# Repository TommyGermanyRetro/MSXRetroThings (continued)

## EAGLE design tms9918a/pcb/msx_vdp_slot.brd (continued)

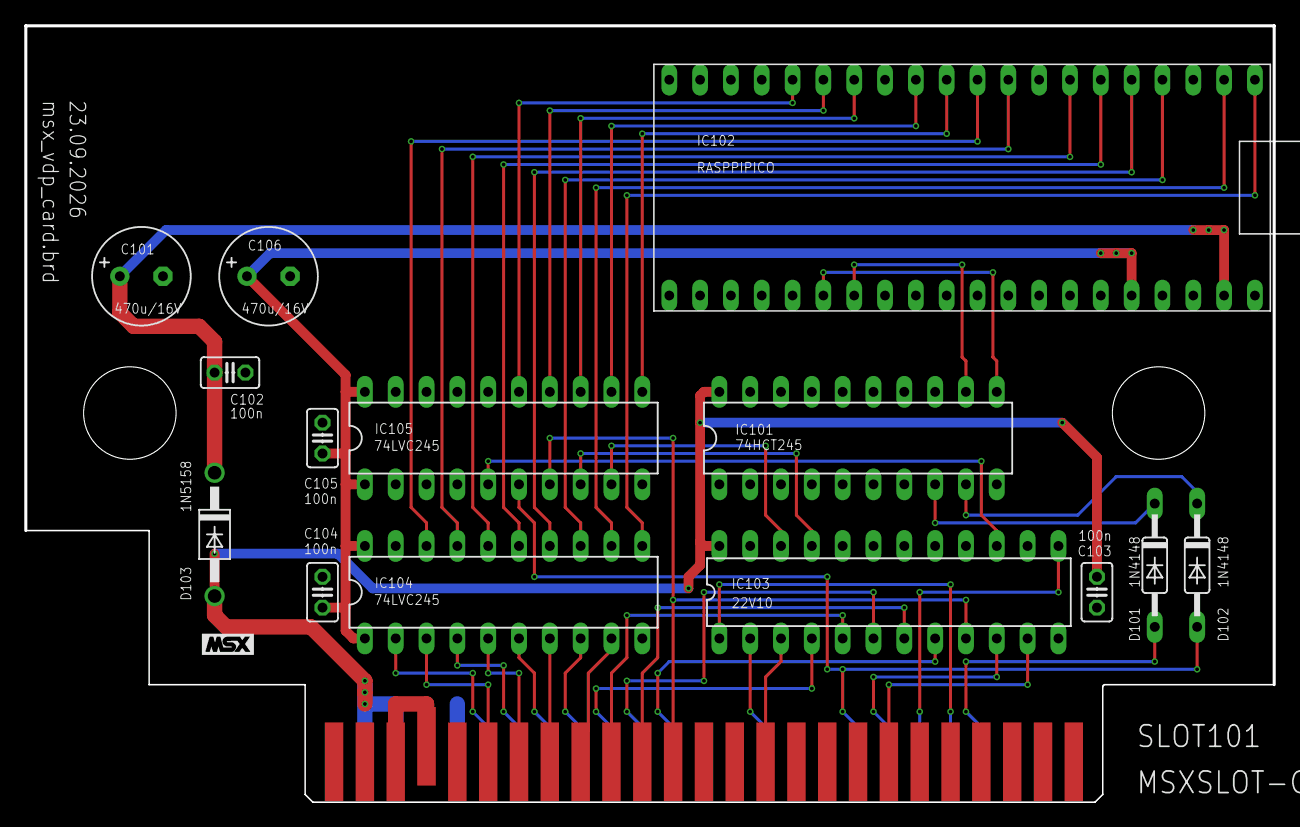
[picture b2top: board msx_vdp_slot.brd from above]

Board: 2 copper layers, 102.9 x 64.0 mm, 15 parts (0 on the bottom side), 47 nets.

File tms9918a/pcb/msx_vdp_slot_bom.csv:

Qty,Reference,Value,Package,Description
1,IC102,Raspberry Pi Pico,RASPPIPICO,"Raspberry Pi Pico (RP2040), flashed with TMS9918aPiPico.ino.uf2"
1,IC103,GAL22V10D,DIL24-3,"GAL22V10D-7LPN (or faster), programmed with gal/FPGA_IO.jed: decodes ports 98h/99h, /CSR and /CSW"
2,"IC104, IC105",74LVC245,DIL20,"Octal bus transceiver, slot to Pico (5 V tolerant in, 3.3 V out)"
1,IC101,74HCT245,DIL20,"Octal bus transceiver, Pico to slot (3.3 V in, 5 V out) for /WAIT and the reset of the MSX"
1,SLOT101,MSX card,MSXCARD,"MSX cartridge edge connector, 50 pins (2 x 25), 2.54 mm pitch, part of the board"
1,D103,1N5818,DO41-10,"Schottky diode, slot +5 V to Pico VSYS"
2,"D101, D102",1N4148,DO35-10,"Signal diode, 74HCT245 pulls /WAIT and /RESET of the slot only LOW"
2,"C101, C106",470u/16V,E3.5-8,"Electrolytic capacitor 470 uF 16 V, radial, 3.5 mm pitch, 8 mm diameter (C101 Pico VSYS, C106 +3.3 V)"
4,"C102, C103, C104, C105",100n,C025-025X050,"Ceramic capacitor 100 nF, 2.5 mm pitch"

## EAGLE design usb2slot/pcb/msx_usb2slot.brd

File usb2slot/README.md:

# USB2SLOT - real MSX cartridges in openMSX

USB2SLOT connects real MSX cartridges to the openMSX emulator on a Windows PC. A Teensy 4.1 on a small board
with two MSX cartridge slots generates the MSX clock and runs genuine Z80 bus cycles on the cartridges. openMSX
gets a new device, `USBSlot`, that forwards every memory and I/O access of its slot over USB to the board.

Tested with ROM cartridges (RCX, XIO), a cartridge with its own slot expander, the SD Mapper/Megaram 512K
cartridge (Nextor boots from its SD card, Memory Mapper and MegaRAM mode) and the RC2014 cards behind the RCX/XIO
cartridges (I/O, /INT and /WAIT), on emulated Spectravideo SVI-728 and Philips VG-8235 machines.

**Videos: booting Nextor from a real cartridge.** Both machines are emulated by openMSX, the cartridge is real: the SD Mapper/Megaram 512K sits in slot 2 of the board, and openMSX reaches it only over USB. From power-on, the machine scans its slots, finds the Nextor ROM of the cartridge, loads NEXTOR.SYS and COMMAND2.COM from the SD card of the cartridge and stops at the `A:\>` prompt. The videos were recorded in emulated time, so they run at the speed of a real MSX. With firmware protocol 3 the PC is faster than that: openMSX reaches the prompt of the VG-8235 after about 6 seconds, because the SD card sectors come over USB in one block each (see [CARTRIDGE_PROFILES.md](CARTRIDGE_PROFILES.md)). Click a picture to open the video.

Philips VG-8235 (MSX2), prompt after 18 seconds

Spectravideo SVI-728 (MSX1), prompt after 17 seconds

## Contents of this folder

| Folder | Content |
| --- | --- |
| [pcb](pcb) | Eagle project of the board: schematic `msx_usb2slot.sch`, layout `msx_usb2slot.brd`; bill of materials `msx_usb2slot_bom.csv`; photos |
| [case](case) | 3D-printable enclosure, bottom and top part as FreeCAD files `MSX_USB2SLOT_BOTTOM.FCStd` and `MSX_USB2SLOT_TOP.FCStd` |
| [pcb/gerber](pcb/gerber) | Gerber RS-274X and Excellon drill files of the two-layer board, also as `msx_usb2slot_gerber.zip` for the PCB maker |
| [firmware](firmware) | Teensy firmware `BridgeTeensy/BridgeTeensy.ino` and the ready-to-flash `BridgeTeensy.ino.hex` |
| [slotlink](slotlink) | PC library `slotlink.h` (Win32) and the test tool `slottest.exe` with its source |
| [openmsx](openmsx) | The `USBSlot` device (`USBSlot.cc/.hh`), start script, extensions, build scripts |
| [media](media) | Videos: start of a VG-8235 and an SVI-728 to the Nextor prompt |
| [CARTRIDGE_PROFILES.md](CARTRIDGE_PROFILES.md) | Recipe for cartridges with their own logic (slot expander, bank registers, SPI ports): detection, cache rules, block reads, measuring; worked example SD Mapper |
| [openmsx/bin](openmsx/bin) | Ready-to-run openMSX 21.0 for Windows x64 with the `USBSlot` device built in |

## 1. Hardware

- Teensy 4.1, two 50-pin MSX cartridge slots, level shifters 74HCT245 (Teensy to slot, 5 V) and 74LVC245 (slot to
  Teensy, 3.3 V); the data bus has one write path (74HCT245) and one read path (74LVC245).
- Power: external 5 V supply, at least 2 A (300 mA per slot plus Teensy and level shifters). +12 V and -12 V for the
  slots come from a DC-DC module. The Teensy is fed from the slot supply through a Schottky diode on VIN, so it
  stays powered whenever the slots are.
- If VIN and VUSB of the Teensy are connected (check with a continuity tester), the slot supply can feed current
  into the USB port of a switched-off PC. Keep that in mind when the PC is off and the cable stays plugged in.
- Jumper JP201: open for normal use. 1-2 connects the Teensy test line to /WAIT, 3-4 to /INT; both are only for
  the self test of the board (see section 3).
- No hot plug, just like a real MSX: change cartridges only with the board switched off.
- To order the board, upload `pcb/gerber/msx_usb2slot_gerber.zip` to the PCB maker. Check the layers in a Gerber
  viewer (for example the online viewer of the PCB maker) before you order. The parts are listed in
  `pcb/msx_usb2slot_bom.csv`.

### Enclosure

`case` holds a two-part enclosure for the board (outside 150 x 115 mm; bottom part 10 mm, top part
30 mm high) as FreeCAD files, built with FreeCAD 1.0 (PartDesign: sketches, pads, pockets). Only the
design files are included, no STL or G-code, so the enclosure can be adapted, for example to other
cartridges, a different supply socket or another printer, before printing:

1. Open `MSX_USB2SLOT_BOTTOM.FCStd` and `MSX_USB2SLOT_TOP.FCStd` in FreeCAD 1.0 or newer and change the
   sketches as needed; the following features update automatically.
2. Select the body and export it as STL or 3MF (File > Export).
3. Slice the file for your printer as usual.

## 2. Firmware

The firmware runs on a Teensy 4.1 (USB type "Serial", CPU speed 600 MHz).

- Easiest way: open `firmware/BridgeTeensy.ino.hex` in the Teensy Loader (part of Teensyduino) and press the
  button on the Teensy.
- Or build it yourself with the Teensy core (`teensy:avr`):

  ```text
  arduino-cli compile --fqbn teensy:avr:teensy41:usb=serial,speed=600 --output-dir build firmware/BridgeTeensy
  arduino-cli upload  --fqbn teensy:avr:teensy41:usb=serial,speed=600 --input-dir build -p <COMx> firmware/BridgeTeensy
  ```

After flashing, the Teensy appears as a serial port (COM port). Look up its number in the Windows Device Manager;
all examples below use `COM16`.

The firmware speaks binary protocol version 3 (spaced block reads `MRDNG` for ports that need time per byte).
openMSX and `slottest` of this folder also accept a board with protocol 2; then the SD card of the SD Mapper is
read byte by byte, as before, and much slower. After an update of this folder, flash the new `.hex` as well.

## 3. Check the board

`slotlink/slottest.exe` talks to the board directly (rebuild it with `slotlink/build.cmd`, Visual Studio 2022):

```text
slottest COM16 hello       version and state of the board
slottest COM16 scan        what is plugged in: slot expander, ROM/data/empty per subslot, Nextor driver name, MegaROM mapper, I/O ports
slottest COM16 selftest    protocol self test
slottest COM16 dump 1 4000 4000 rom.bin    read 16 KB from slot 1, address 4000h, into rom.bin
slottest COM16 clock 0     set the clock of RC2014 card A (PCF8584 at I/O address 0) to the PC time
```

`clock` uses the registers of `CALL SET TIME` and `CALL SET DATE` of the RCX ROM. It writes only when switched I/O
answers, the RCX ROM ("RCX_INTERFACE" at 4010h) is in a slot or subslot of the board, the PCF8584 is idle after its
initialisation and the PCF8583 acknowledges its address A0h; it prints `CLOCK SET`, or `NOSWIO`, `NORCX`,
`NOCONTROLLER` or `NOCLOCK` for the check that failed. The address is decimal, as in `CALL I2C INIT`.

`slottest` without parameters lists all commands. The self test checks /INT and /WAIT through jumper JP201; with
the jumper open those two checks fail, all others must pass.

## 4. Start openMSX with the board

Requirements: Windows 10/11 x64 and Python 3. No installation of openMSX is needed; `openmsx/bin` is a complete
openMSX 21.0.

```text
openmsx\start_usbslot.cmd [machine] [--port COMx] [--bridge 1|2|12] [--clock [address]] [more openMSX parameters]
```

The script first asks the board what is plugged in (`slottest scan`), writes matching extensions to
`Documents\openMSX\share\extensions` (`USBSlotAuto1`, `USBSlotAuto2`, `USBSlotAutoIO`) and then starts
`openmsx\bin\openmsx.exe` with them. It detects:

- a cartridge without slot expander; for a MegaROM the mapper type (Konami, Konami SCC, ASCII8, ASCII16) is guessed
  like openMSX does, from the `LD (nnnn),A` to the bank registers in the 32 KB at 4000h-BFFFh (at least three hits),
- a cartridge with its own slot expander (contents of each subslot),
- the SD Mapper/Megaram 512K cartridge, either as Memory Mapper (ports FCh-FFh) or as MegaRAM (ports 8Eh/8Fh);
  only when ROM bank 7 holds the Nextor driver "SDMapper Driver", otherwise it counts as a plain slot expander,
- RCX/XIO cartridges with switched I/O on ports 40h-47h.

Examples:

```text
openmsx\start_usbslot.cmd
openmsx\start_usbslot.cmd Spectravideo_SVI-728 --port COM5
openmsx\start_usbslot.cmd Philips_VG_8235-00 --bridge 1 -cartb game.rom
```

- `--port`: COM port of the board, default `COM16` (or the environment variable `USBSLOT_PORT`).
- `--bridge 1`, `2` or `12`: use only these slots of the board (see next section).
- `--clock [address]`: on MSX1 machines (`<type>MSX</type>` in the machine description) set the clock of RC2014
  card A to the PC time with `slottest clock` before openMSX starts; the address of its PCF8584 is decimal,
  default 0. Without `--clock` the clock is left alone.
- Without a machine name the script uses `C-BIOS_MSX2+_JP`.

### Mixing real and emulated cartridges

Real cartridges on the board and cartridges emulated by openMSX (ROM images, openMSX extensions) can run side by
side in one machine.

- Each slot of the board takes one free cartridge slot of the emulated machine. The switched I/O ports 40h-47h
  (`USBSlotAutoIO`) take no slot.
- All parameters that are not for the script itself (`-carta`, `-cartb`, `-exta`, `-ext`, ...) are passed to
  openMSX before the board's extensions. openMSX fills these fixed slots first; the slots of the board get the
  slots that are still free.
- A machine with two cartridge slots has no free slot left when both slots of the board are in use. Then
  `--bridge 1` or `--bridge 2` takes only one slot of the board into the emulation and leaves the other machine
  slot for the emulated cartridge. The script reports a board slot it leaves out as "not included".

Examples:

```text
rem ROM image in machine slot 1, the cartridge in slot 1 of the board in machine slot 2
openmsx\start_usbslot.cmd Spectravideo_SVI-728 --bridge 1 -carta game.rom

rem openMSX extension (1 MB Memory Mapper) in one machine slot, slot 2 of the board in the other
openmsx\start_usbslot.cmd Philips_VG_8235-00 --bridge 2 -ext ram1mb
```

`slotmap` in the openMSX console shows which cartridge ended up in which slot.

### Machines and system ROMs

The cartridges themselves need no ROM files: their ROMs sit on the real cartridges. The emulated machine does:

- C-BIOS (free, part of openMSX) works out of the box, but it has no MSX-BASIC. BASIC programs and CALL commands
  of cartridges (e.g. `_RCX`, `_XIO`) need a real machine.
- For real machines such as the Spectravideo SVI-728 or the Philips VG-8235, copy your own dumps of the system ROMs
  to `Documents\openMSX\share\systemroms`. openMSX finds them by their SHA1 checksum. System ROMs are not part of
  this repository.

### Behaviour during emulation

- Every slot access of the emulated CPU goes to the real cartridge. A read cache keeps ROM contents on the PC, so
  ROM software runs in real time; I/O ports and areas marked `<nocache>` are always accessed directly.
- SD Mapper: the Nextor ROM is cached as long as the SPI port of the SD cards is switched off (6001h). The driver
  reads a sector with 512 `LDI` (a card register with 16); the bridge reads the bytes that chain will take in one
  block, 24 clocks apart, as the SPI logic of the cartridge needs it.
- /INT of the cartridges reaches the emulated CPU. /WAIT of memory reads and of I/O cycles is added to the
  emulated time.
- While openMSX runs, it sends a heartbeat to the board. When the emulation stops for more than 200 ms (pause,
  debugger), the board switches the cartridges off like a powered-down MSX; on resume openMSX notices this and
  resets the machine.
- If the USB connection breaks, the slot reads FFh until the next reset of the machine; the reset reconnects.

## 5. Extensions written by hand

`openmsx/extensions` holds fixed extensions for manual use (copy them to `Documents\openMSX\share\extensions`,
`openmsx/apply.py` does this as well). They contain the COM port in `<port>`; adjust it to your board.

| Extension | Content |
| --- | --- |
| `USBSlot1`, `USBSlot2` | slot 1 or 2 of the board, plain cartridge |
| `USBSlot1_Expander` | slot 1 with a cartridge that has its own slot expander |
| `USBSlot1_SDMapper`, `USBSlot2_SDMapper` | SD Mapper/Megaram 512K as Memory Mapper |
| `USBSlot2_SDMegaRAM` | SD Mapper/Megaram 512K as MegaRAM |
| `USBSlotIO40` | I/O ports 40h-47h (switched I/O) of the cartridges on the board |

Start example: `openmsx\bin\openmsx.exe -machine Spectravideo_SVI-728 -ext USBSlot1 -ext USBSlotIO40`

Rules inside `<USBSlot>` that tell the read cache how the cartridge switches its memory:

| Rule | Effect |
| --- | --- |
| `<expander>true</expander>` | the cartridge has its own slot expander (register FFFFh); rules per subslot in `<subslot id="0..3">` |
| `<nocache base=".." size=".."/>` | area is always read directly (registers, status, ports) |
| `<nocacheswitch address="0x6001" base="0x4000" size="0x0801"/>` | area is read directly only while bit 0 of the last write to the address is set (SD Mapper: SPI port instead of the Nextor ROM) |
| `<spiblock start="0x4001" end="0x41FF" gap="24"/>` | when an `LDI` of the cartridge's ROM reads `start` through the switched port, the bytes of the `LDI` that follow it in the code (at most up to `end`) are read in one block, `gap` clocks per byte (protocol 3) |
| `<bank page="1" address="0x6000" mask="0x07"/>` | a write to the address selects the ROM bank of the page |
| `<mapper port="0xFC" mask="0x1F"/>` | Memory Mapper RAM, segments selected by ports FCh-FFh |
| `<megaram port="0x8E"/>` | MegaRAM with four 8 KB bank registers, switched by ports 8Eh/8Fh |
| `<rommapper type="konami"/>` | ROM mapper of a MegaROM: `konami`, `konamiscc` (3Fh at 9000h shows the SCC at 9800h-9FFFh, never cached), `ascii8` or `ascii16`; writes to 4000h-BFFFh switch the 8 KB banks, one cache image per bank. Checked with simulated cartridges only so far |

## 6. Build openMSX yourself

Needed: Visual Studio 2022 (C++ workload), Git, Python 3.

```text
git clone --branch RELEASE_21_0 https://github.com/openMSX/openMSX.git C:\openMSX-21.0
cd C:\openMSX-21.0
python build\thirdparty_download.py windows
<this folder>\openmsx\build3rd.cmd C:\openMSX-21.0
python <this folder>\openmsx\apply.py C:\openMSX-21.0
<this folder>\openmsx\buildomsx.cmd C:\openMSX-21.0
```

- `apply.py` copies `USBSlot.cc/.hh` and `slotlink/slotlink.h` to `src/memory`, adds the device to
  `src/DeviceFactory.cc` and to the MSVC project, and installs the extensions. Running it twice changes nothing.
- The build scripts expect Visual Studio 2022 Community; for another edition adjust the path to `vcvars64.bat`.
- The result is `derived\x64-VC-Release\install\openmsx.exe`. Copy it to `openmsx\bin`, or point the start script
  to it with the environment variables `USBSLOT_OPENMSX` (path of `openmsx.exe`) and `USBSLOT_SHARE` (path of the
  `share` folder of an openMSX 21.0 installation).

## 7. Limitations

- Windows only (the USB connection uses the Win32 API).
- /M1 reaches the cartridge only in areas marked `<nocache>`; cached instructions never appear on the bus.
- /WAIT during memory writes is not added to the emulated time (no cartridge known to need it).
- Cartridges with an unknown slot expander or mapper run without switching rules; the cache then may show stale
  contents after a bank switch. Add matching rules to the extension.
- Uncached accesses take a USB round trip of about 100 microseconds. With firmware protocol 3 the SD card of the SD
  Mapper is about as fast as on a real MSX (`dir` in openMSX 4 s instead of 15 s byte by byte); cached ROM code runs in real
  time. Other cartridges with ports that need time per byte need their own profile, see
  [CARTRIDGE_PROFILES.md](CARTRIDGE_PROFILES.md).
- Not tested yet: game cartridges with their own mapper (Konami, ASCII, SCC), FM-PAC.

## 8. License

The parts in this folder follow the [license of this repository](../README.md#9-license): software MIT, the board
and the enclosure CERN-OHL-S-2.0, documentation CC BY-SA 4.0.

`openmsx/bin` is openMSX 21.0 (GNU General Public License version 2, see `openmsx/bin/doc/GPL.txt`) with the
`USBSlot` device built in, including C-BIOS (see `openmsx/bin/doc/cbios.txt`). Its complete source is openMSX
21.0 (https://github.com/openMSX/openMSX, tag `RELEASE_21_0`) plus the files in `openmsx` and `slotlink`, combined
with `openmsx/apply.py` as described in section 6.

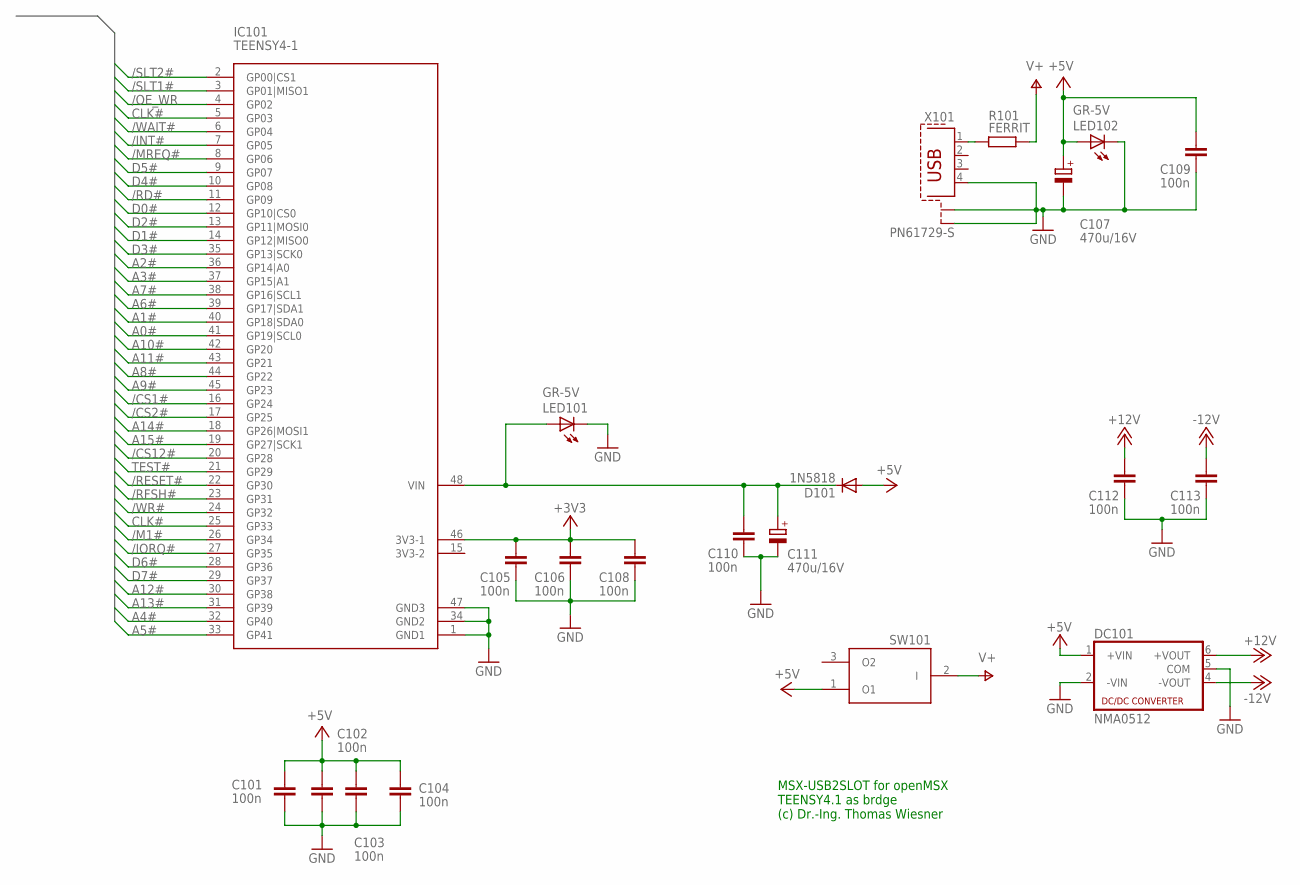
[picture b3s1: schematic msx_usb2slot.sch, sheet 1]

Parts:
C101, C102, C103, C104, C105, C106, C108, C109, C110, C112, C113: 100n; C025-025X050
C107, C111: 470u/16V; E3,5-8
D101: 1N5818; DO41-10
DC101: NMA0512; NMA
IC101: TEENSY4-1
LED101, LED102: GR-5V; LED3MM
R101: FERRIT; 0207/10
SW101: TS-13PA; TS-13-P
X101: PN61729-S

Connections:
+3V3: C105.2, C106.2, C108.2, IC101.46 (3V3-1); also elsewhere on the board
+5V: C101.2, C102.2, C103.2, C104.2, C107.+, C109.2, D101.A, DC101.1 (+VIN), LED102.A, SW101.1 (O1); also elsewhere on the board
+12V: C112.2, DC101.6 (+VOUT); also elsewhere on the board
-12V: C113.2, DC101.4 (-VOUT); also elsewhere on the board
/CS1#: IC101.16 (GP24); also elsewhere on the board
/CS2#: IC101.17 (GP25); also elsewhere on the board
/CS12#: IC101.20 (GP28); also elsewhere on the board
/INT#: IC101.7 (GP05); also elsewhere on the board
/IORQ#: IC101.27 (GP35); also elsewhere on the board
/M1#: IC101.26 (GP34); also elsewhere on the board
/MREQ#: IC101.8 (GP06); also elsewhere on the board
/OE_WR: IC101.4 (GP02); also elsewhere on the board
/RD#: IC101.11 (GP09); also elsewhere on the board
/RESET#: IC101.22 (GP30); also elsewhere on the board
/RFSH#: IC101.23 (GP31); also elsewhere on the board
/SLT1#: IC101.3 (GP01|MISO1); also elsewhere on the board
/SLT2#: IC101.2 (GP00|CS1); also elsewhere on the board
/WAIT#: IC101.6 (GP04); also elsewhere on the board
/WR#: IC101.24 (GP32); also elsewhere on the board
A0#: IC101.41 (GP19|SCL0); also elsewhere on the board
A1#: IC101.40 (GP18|SDA0); also elsewhere on the board
A2#: IC101.36 (GP14|A0); also elsewhere on the board
A3#: IC101.37 (GP15|A1); also elsewhere on the board
A4#: IC101.32 (GP40); also elsewhere on the board
A5#: IC101.33 (GP41); also elsewhere on the board
A6#: IC101.39 (GP17|SDA1); also elsewhere on the board
A7#: IC101.38 (GP16|SCL1); also elsewhere on the board
A8#: IC101.44 (GP22); also elsewhere on the board
A9#: IC101.45 (GP23); also elsewhere on the board
A10#: IC101.42 (GP20); also elsewhere on the board
A11#: IC101.43 (GP21); also elsewhere on the board
A12#: IC101.30 (GP38); also elsewhere on the board
A13#: IC101.31 (GP39); also elsewhere on the board
A14#: IC101.18 (GP26|MOSI1); also elsewhere on the board
A15#: IC101.19 (GP27|SCK1); also elsewhere on the board
CLK#: IC101.5 (GP03), IC101.25 (GP33); also elsewhere on the board
D0#: IC101.12 (GP10|CS0); also elsewhere on the board
D1#: IC101.14 (GP12|MISO0); also elsewhere on the board
D2#: IC101.13 (GP11|MOSI0); also elsewhere on the board
D3#: IC101.35 (GP13|SCK0); also elsewhere on the board
D4#: IC101.10 (GP08); also elsewhere on the board
D5#: IC101.9 (GP07); also elsewhere on the board
D6#: IC101.28 (GP36); also elsewhere on the board
D7#: IC101.29 (GP37); also elsewhere on the board
GND: C101.1, C102.1, C103.1, C104.1, C105.1, C106.1, C107.-, C108.1, C109.1, C110.1, C111.-, C112.1, C113.1, DC101.2 (-VIN), DC101.5 (COM), IC101.1 (GND1), IC101.34 (GND2), IC101.47 (GND3), LED101.K (C), LED102.K (C), X101.4, X101.S1, X101.S2; also elsewhere on the board
unnamed: C110.2, C111.+, D101.C, IC101.48 (VIN), LED101.A
unnamed: R101.2, X101.1
TEST#: IC101.21 (GP29); also elsewhere on the board
V+: R101.1, SW101.2 (I)

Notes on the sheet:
MSX-USB2SLOT for openMSX TEENSY4.1 as brdge (c) Dr.-Ing. Thomas Wiesner

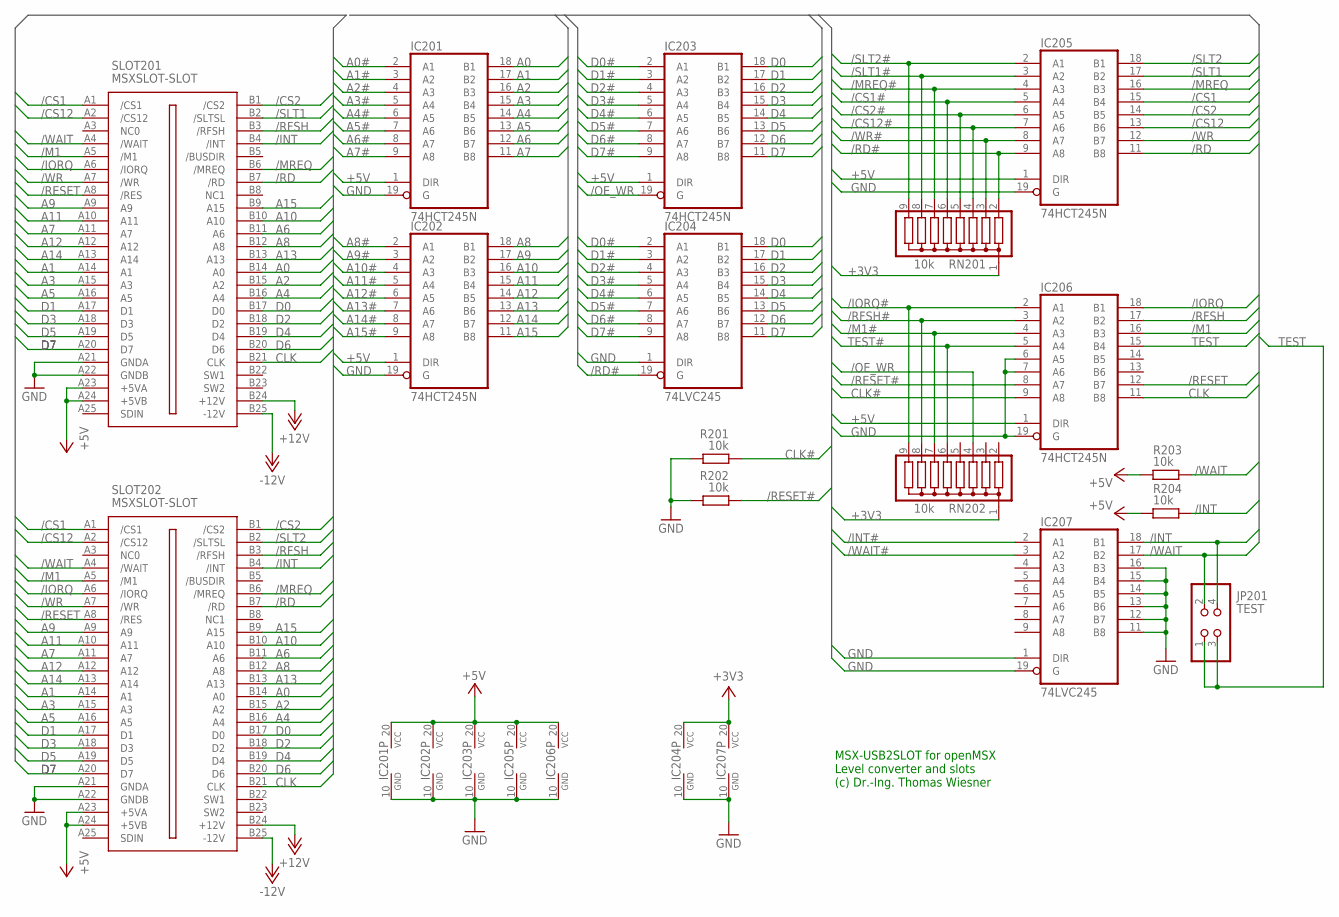
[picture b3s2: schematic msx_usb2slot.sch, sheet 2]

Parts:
IC201, IC202, IC203, IC205, IC206: 74HCT245N; DIL20
IC204, IC207: 74LVC245; DIL20
JP201: TEST; 2X02
R201, R202, R203, R204: 10k; 0207/10
RN201, RN202: 10k; SIL9
SLOT201, SLOT202: MSXSLOT-SLOT; MSXSLOT

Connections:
+3V3: IC204.20 (VCC), IC207.20 (VCC), RN201.1, RN202.1; also elsewhere on the board
+5V: IC201.1 (DIR), IC201.20 (VCC), IC202.1 (DIR), IC202.20 (VCC), IC203.1 (DIR), IC203.20 (VCC), IC205.1 (DIR), IC205.20 (VCC), IC206.1 (DIR), IC206.20 (VCC), R203.2, R204.2, SLOT201.A23 (+5VA), SLOT201.A24 (+5VB), SLOT202.A23 (+5VA), SLOT202.A24 (+5VB); also elsewhere on the board
+12V: SLOT201.B24 (+12V), SLOT202.B24 (+12V); also elsewhere on the board
-12V: SLOT201.B25 (-12V), SLOT202.B25 (-12V); also elsewhere on the board
/CS1: IC205.15 (B4), SLOT201.A1 (/CS1), SLOT202.A1 (/CS1)
/CS1#: IC205.5 (A4), RN201.6; also elsewhere on the board
/CS2: IC205.14 (B5), SLOT201.B1 (/CS2), SLOT202.B1 (/CS2)
/CS2#: IC205.6 (A5), RN201.5; also elsewhere on the board
/CS12: IC205.13 (B6), SLOT201.A2 (/CS12), SLOT202.A2 (/CS12)
/CS12#: IC205.7 (A6), RN201.4; also elsewhere on the board
/INT: IC207.18 (B1), JP201.4, R204.1, SLOT201.B4 (/INT), SLOT202.B4 (/INT)
/INT#: IC207.2 (A1); also elsewhere on the board
/IORQ: IC206.18 (B1), SLOT201.A6 (/IORQ), SLOT202.A6 (/IORQ)
/IORQ#: IC206.2 (A1), RN202.9; also elsewhere on the board
/M1: IC206.16 (B3), SLOT201.A5 (/M1), SLOT202.A5 (/M1)
/M1#: IC206.4 (A3), RN202.7; also elsewhere on the board
/MREQ: IC205.16 (B3), SLOT201.B6 (/MREQ), SLOT202.B6 (/MREQ)
/MREQ#: IC205.4 (A3), RN201.7; also elsewhere on the board
/OE_WR: IC203.19 (G), RN202.4; also elsewhere on the board
/RD: IC205.11 (B8), SLOT201.B7 (/RD), SLOT202.B7 (/RD)
/RD#: IC204.19 (G), IC205.9 (A8), RN201.2; also elsewhere on the board
/RESET: IC206.12 (B7), SLOT201.A8 (/RES), SLOT202.A8 (/RES)
/RESET#: IC206.8 (A7), R202.2; also elsewhere on the board
/RFSH: IC206.17 (B2), SLOT201.B3 (/RFSH), SLOT202.B3 (/RFSH)
/RFSH#: IC206.3 (A2), RN202.8; also elsewhere on the board
/SLT1: IC205.17 (B2), SLOT201.B2 (/SLTSL)
/SLT1#: IC205.3 (A2), RN201.8; also elsewhere on the board
/SLT2: IC205.18 (B1), SLOT202.B2 (/SLTSL)
/SLT2#: IC205.2 (A1), RN201.9; also elsewhere on the board
/WAIT: IC207.17 (B2), JP201.2, R203.1, SLOT201.A4 (/WAIT), SLOT202.A4 (/WAIT)
/WAIT#: IC207.3 (A2); also elsewhere on the board
/WR: IC205.12 (B7), SLOT201.A7 (/WR), SLOT202.A7 (/WR)
/WR#: IC205.8 (A7), RN201.3; also elsewhere on the board
A0: IC201.18 (B1), SLOT201.B14 (A0), SLOT202.B14 (A0)
A0#: IC201.2 (A1); also elsewhere on the board
A1: IC201.17 (B2), SLOT201.A14 (A1), SLOT202.A14 (A1)
A1#: IC201.3 (A2); also elsewhere on the board
A2: IC201.16 (B3), SLOT201.B15 (A2), SLOT202.B15 (A2)
A2#: IC201.4 (A3); also elsewhere on the board
A3: IC201.15 (B4), SLOT201.A15 (A3), SLOT202.A15 (A3)
A3#: IC201.5 (A4); also elsewhere on the board
A4: IC201.14 (B5), SLOT201.B16 (A4), SLOT202.B16 (A4)
A4#: IC201.6 (A5); also elsewhere on the board
A5: IC201.13 (B6), SLOT201.A16 (A5), SLOT202.A16 (A5)
A5#: IC201.7 (A6); also elsewhere on the board
A6: IC201.12 (B7), SLOT201.B11 (A6), SLOT202.B11 (A6)
A6#: IC201.8 (A7); also elsewhere on the board
A7: IC201.11 (B8), SLOT201.A11 (A7), SLOT202.A11 (A7)
A7#: IC201.9 (A8); also elsewhere on the board
A8: IC202.18 (B1), SLOT201.B12 (A8), SLOT202.B12 (A8)
A8#: IC202.2 (A1); also elsewhere on the board
A9: IC202.17 (B2), SLOT201.A9, SLOT202.A9
A9#: IC202.3 (A2); also elsewhere on the board
A10: IC202.16 (B3), SLOT201.B10 (A10), SLOT202.B10 (A10)
A10#: IC202.4 (A3); also elsewhere on the board
A11: IC202.15 (B4), SLOT201.A10 (A11), SLOT202.A10 (A11)
A11#: IC202.5 (A4); also elsewhere on the board
A12: IC202.14 (B5), SLOT201.A12, SLOT202.A12
A12#: IC202.6 (A5); also elsewhere on the board
A13: IC202.13 (B6), SLOT201.B13 (A13), SLOT202.B13 (A13)
A13#: IC202.7 (A6); also elsewhere on the board
A14: IC202.12 (B7), SLOT201.A13 (A14), SLOT202.A13 (A14)
A14#: IC202.8 (A7); also elsewhere on the board
A15: IC202.11 (B8), SLOT201.B9 (A15), SLOT202.B9 (A15)
A15#: IC202.9 (A8); also elsewhere on the board
CLK: IC206.11 (B8), SLOT201.B21 (CLK), SLOT202.B21 (CLK)
CLK#: IC206.9 (A8), R201.2; also elsewhere on the board
D0: IC203.18 (B1), IC204.18 (B1), SLOT201.B17 (D0), SLOT202.B17 (D0)
D0#: IC203.2 (A1), IC204.2 (A1); also elsewhere on the board
D1: IC203.17 (B2), IC204.17 (B2), SLOT201.A17 (D1), SLOT202.A17 (D1)
D1#: IC203.3 (A2), IC204.3 (A2); also elsewhere on the board
D2: IC203.16 (B3), IC204.16 (B3), SLOT201.B18 (D2), SLOT202.B18 (D2)
D2#: IC203.4 (A3), IC204.4 (A3); also elsewhere on the board
D3: IC203.15 (B4), IC204.15 (B4), SLOT201.A18 (D3), SLOT202.A18 (D3)
D3#: IC203.5 (A4), IC204.5 (A4); also elsewhere on the board
D4: IC203.14 (B5), IC204.14 (B5), SLOT201.B19 (D4), SLOT202.B19 (D4)
D4#: IC203.6 (A5), IC204.6 (A5); also elsewhere on the board
D5: IC203.13 (B6), IC204.13 (B6), SLOT201.A19 (D5), SLOT202.A19 (D5)
D5#: IC203.7 (A6), IC204.7 (A6); also elsewhere on the board
D6: IC203.12 (B7), IC204.12 (B7), SLOT201.B20 (D6), SLOT202.B20 (D6)
D6#: IC203.8 (A7), IC204.8 (A7); also elsewhere on the board
D7: IC203.11 (B8), IC204.11 (B8), SLOT201.A20 (D7), SLOT202.A20 (D7)
D7#: IC203.9 (A8), IC204.9 (A8); also elsewhere on the board
GND: IC201.10 (GND), IC201.19 (G), IC202.10 (GND), IC202.19 (G), IC203.10 (GND), IC204.1 (DIR), IC204.10 (GND), IC205.10 (GND), IC205.19 (G), IC206.6 (A5), IC206.7 (A6), IC206.10 (GND), IC206.19 (G), IC207.1 (DIR), IC207.10 (GND), IC207.11 (B8), IC207.12 (B7), IC207.13 (B6), IC207.14 (B5), IC207.15 (B4), IC207.16 (B3), IC207.19 (G), R201.1, R202.1, SLOT201.A21 (GNDA), SLOT201.A22 (GNDB), SLOT202.A21 (GNDA), SLOT202.A22 (GNDB); also elsewhere on the board
TEST: IC206.15 (B4), JP201.1, JP201.3
TEST#: IC206.5 (A4), RN202.6; also elsewhere on the board

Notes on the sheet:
MSX-USB2SLOT for openMSX Level converter and slots (c) Dr.-Ing. Thomas Wiesner

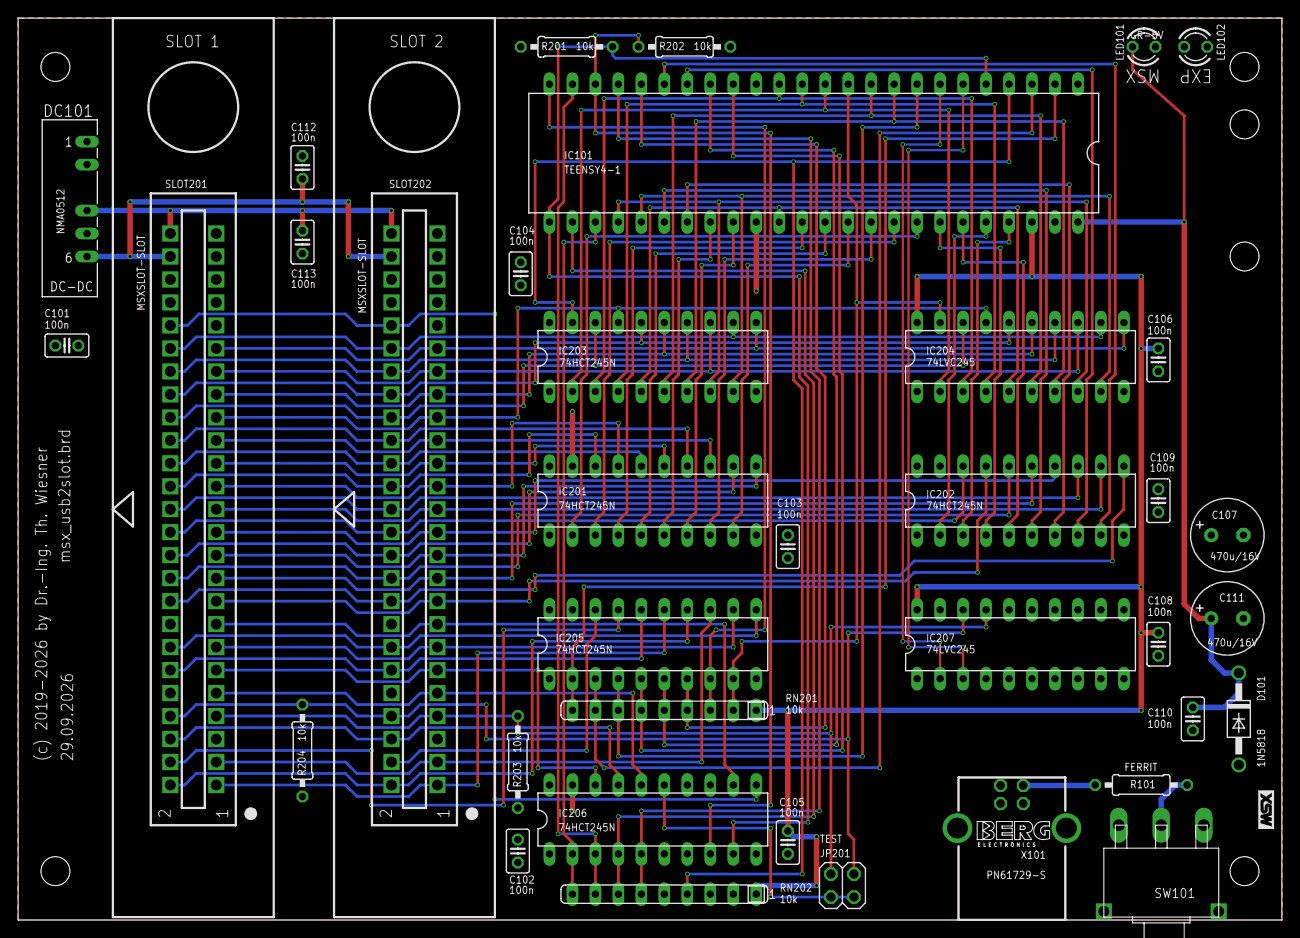
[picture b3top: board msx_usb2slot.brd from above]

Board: 2 copper layers, 139.7 x 99.7 mm, 37 parts (0 on the bottom side), 89 nets.

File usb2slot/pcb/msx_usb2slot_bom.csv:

Qty,Reference,Value,Package,Description
1,IC101,Teensy 4.1,TEENSY4-1,Teensy 4.1 microcontroller board (PJRC) with pin headers
5,"IC201, IC202, IC203, IC205, IC206",74HCT245N,DIL20,"Octal bus transceiver, Teensy to slot (3.3 V in, 5 V out)"
2,"IC204, IC207",74LVC245,DIL20,"Octal bus transceiver, slot to Teensy (5 V tolerant in, 3.3 V out)"
2,"SLOT201, SLOT202",MSX slot,MSXSLOT,"MSX cartridge slot, 50 pins (2 x 25), 2.54 mm pitch"
1,DC101,NMA0512,NMA,"DC-DC converter 5 V to +12 V / -12 V (Murata NMA0512SC)"
1,X101,PN61729-S,PN61729-S,"USB type B socket (FCI/Berg PN61729-S), 5 V power input"
1,SW101,TS-13P,TS-13-P,Power switch
1,R101,Ferrite bead,0207/10,"Ferrite bead in the 5 V input, axial, 10 mm pitch"
1,D101,1N5818,DO41-10,"Schottky diode, slot supply to Teensy VIN"
2,"LED101, LED102",GR-5V,LED3MM,"LED 3 mm green with built-in resistor for 5 V (LED101 Teensy VIN, LED102 +5 V)"
2,"C107, C111",470u/16V,E3.5-8,"Electrolytic capacitor 470 uF 16 V, radial, 3.5 mm pitch, 8 mm diameter"
11,"C101, C102, C103, C104, C105, C106, C108, C109, C110, C112, C113",100n,C025-025X050,"Ceramic capacitor 100 nF, 2.5 mm pitch"
4,"R201, R202, R203, R204",10k,0207/10,"Resistor 10 kOhm, axial, 10 mm pitch"
2,"RN201, RN202",10k,SIL9,"Resistor network 8 x 10 kOhm, common pin, SIL9"
1,JP201,TEST,2X02,"Pin header 2 x 2, 2.54 mm, with jumper (open for normal use)"

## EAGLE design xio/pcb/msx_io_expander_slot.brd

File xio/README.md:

# XIO cartridge - command reference

The XIO cartridge provides 256 additional switched IO addresses and an 8259 PIC with an 8-channel daisy-chain Z80 IM2 emulator. Its ROM adds BASIC `CALL` commands and an UNAPI/EXTBIOS interface; the SDCC library `xio_io` bridges to the same functions.

## Command reference

Commands implemented in ROM/LIB:

+ <i><b>XIO ?</i></b>

  Prints the list of available XIO commands directly to the screen. Works independently from XIO INIT, so it is always safe to call even if the card was never installed - useful as a quick "is this ROM extension actually loaded" check.

|  | Definition | BASIC | UNAPI | SDCC |
| --- | --- | --- | --- | --- |
| Syntax | XIO ? | _XIO ? | 1 | - (BASIC-only, not exposed) |

+ <i><b>XIO OUT</i></b>

  Sends a single raw byte to one of the 256 additional switched IO addresses the XIO address decoder provides. Works independently from XIO INIT and the whole interrupt/PIC subsystem - a plain digital output, nothing more.

|  | Definition | BASIC | UNAPI | SDCC |
| --- | --- | --- | --- | --- |
| Syntax | XIO OUT | _XIO OUT() | 2 | Xio_Out() |
| PARA 1 | IO addr 0...255 | byte or variable | C | byte or variable |
| PARA 2 | IO data 0...255 | byte or variable | B | byte or variable |

+ <i><b>XIO INP</i></b>

  Reads a single raw byte back from one of the 256 switched IO addresses. Like XIO OUT, this bypasses XIO INIT and the interrupt system entirely - a plain digital input.

|  | Definition | BASIC | UNAPI | SDCC |
| --- | --- | --- | --- | --- |
| Syntax | XIO INP | _XIO INP() | 3 | Xio_Inp() |
| PARA 1 | IO addr 0...255 | byte or variable | C | byte or variable |
| PARA 2 | IO data 0...255 | variable | DE as varptr | return value (byte) |

+ <i><b>XIO INIT</i></b>

  Installs the XIO card: allocates the BIOS work area and hooks the standard IM2/PIC interrupt dispatcher. The status variable is not read once at install time - the ROM keeps writing into it on every interrupt for the rest of the program's run, one bit per channel (0..15), so a caller can just poll the variable instead of writing its own interrupt handler.

|  | Definition | BASIC | UNAPI | SDCC |
| --- | --- | --- | --- | --- |
| Syntax | XIO INIT | _XIO INIT() | 4 | Xio_Init() |
| PARA 1 | status | variable | DE as varptr | word (intflags) |
| PARA 2 | Working area in RAM | automatic by BIOS | HL | word (workarea) |

+ <i><b>XIO ISINIT</i></b>

  Checks whether XIO is already installed, without touching anything. The usual pattern is ISINIT, then DEINIT if it reports 1, then INIT - so a program never ends up stacking a second installation on top of an old one from a previous run.

|  | Definition | BASIC | UNAPI | SDCC |
| --- | --- | --- | --- | --- |
| Syntax | XIO ISINIT | _XIO ISINIT() | 5 | Xio_IsInit() |
| PARA 1 | 0 = not installed, 1 = installed | variable | DE as varptr | return value (byte) |

+ <i><b>XIO DEINIT</i></b>

  Uninstalls the XIO card: unhooks the interrupt dispatcher and releases the BIOS work area again, so a program can clean up before it exits.

|  | Definition | BASIC | UNAPI | SDCC |
| --- | --- | --- | --- | --- |
| Syntax | XIO DEINIT | _XIO DEINIT | 6 | Xio_Deinit() |

+ <i><b>XIO SET ADDR</i></b>

  Registers a custom Z80 machine code service routine for one of the 16 IM2/PIC channels. Once set, the standard dispatcher calls this routine directly whenever that channel's interrupt fires, instead of only updating the passive status bit that XIO INIT's variable exposes - use this when a channel needs to react immediately rather than being polled.

|  | Definition | BASIC | UNAPI | SDCC |
| --- | --- | --- | --- | --- |
| Syntax | XIO SET ADDR | _XIO SET ADDR() | 7 | Xio_SetAddr() |
| PARA 1 | channel | byte or variable | B | byte or variable |
| PARA 2 | addr | word or variable | DE | word or variable |
| PARA 3 | slot | automatic by BIOS | C | - |

+ <i><b>XIO SET MASK</i></b>

  Enables or disables interrupt channels via a 16-bit bitmask (bit N = channel N). All channels start out disabled after XIO INIT, so this must be called at least once before any channel actually generates interrupts - by convention it is called last, only once the rest of a program's setup (card init, custom SET ADDR routines, etc.) has already completed.

|  | Definition | BASIC | UNAPI | SDCC |
| --- | --- | --- | --- | --- |
| Syntax | XIO SET MASK | _XIO SET MASK() | 8 | Xio_SetMask() |
| PARA 1 | Bit Chx: 0 = disabled, 1 = enabled | word or variable | DE | word or variable |

+ <i><b>XIO GET ADDR</i></b>

  Reads back which service routine address is currently registered for a given channel - the counterpart to XIO SET ADDR, mainly useful for diagnostics.

|  | Definition | BASIC | UNAPI | SDCC |
| --- | --- | --- | --- | --- |
| Syntax | XIO GET ADDR | _XIO GET ADDR() | 9 | Xio_GetAddr() |
| PARA 1 | channel | byte or variable | B | byte or variable |
| PARA 2 | addr | variable | DE as varptr | pointer (word) |
| PARA 3 | slot | automatic by BIOS | C | - |

+ <i><b>XIO GET MASK</i></b>

  Reads back the current 16-bit enable/disable bitmask - the counterpart to XIO SET MASK.

|  | Definition | BASIC | UNAPI | SDCC |
| --- | --- | --- | --- | --- |
| Syntax | XIO GET MASK | _XIO GET MASK() | 10 | Xio_GetMask() |
| PARA 1 | Bit Chx: 0 = disabled, 1 = enabled | variable | DE as varptr | pointer (word) |

## Folders

+ [rom/](rom/README.md) - ROM source and image
+ [basic/](basic/README.md) - BASIC test programs
+ [com/](com/README.md) - `.COM` tools (UNAPI/EXTBIOS)
+ [sdcc/](sdcc/README.md) - SDCC tools
+ [gal/](gal/) - GAL equations
+ [pcb/](pcb/) - schematics, PCB, Gerber and drill files, bill of materials

[↑ Main README](../README.md#1-msxretrothings---the-xio-cartridge)

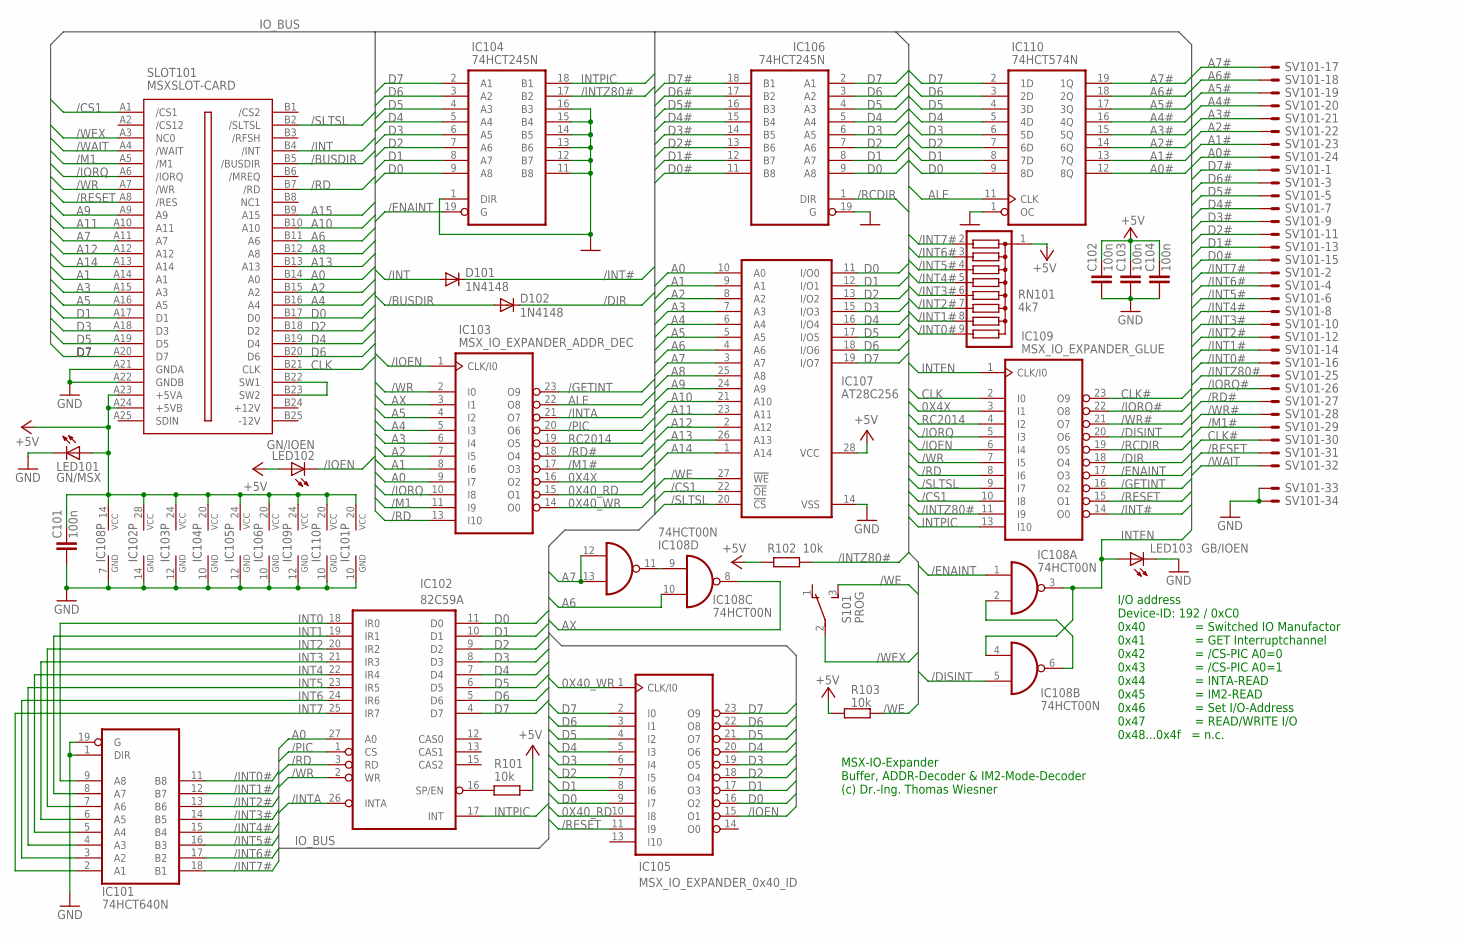
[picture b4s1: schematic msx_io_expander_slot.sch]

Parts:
C101, C102, C103, C104: 100n; C025-025X050
D101, D102: 1N4148; DO35-10
IC101: 74HCT640N; DIL20
IC102: 82C59A; DIL28-6
IC103: MSX_IO_EXPANDER_ADDR_DEC; DIL24-3
IC104, IC106: 74HCT245N; DIL20
IC105: MSX_IO_EXPANDER_0x40_ID; DIL24-3
IC107: AT28C256; DIL28-6
IC108: 74HCT00N; DIL14
IC109: MSX_IO_EXPANDER_GLUE; DIL24-3
IC110: 74HCT574N; DIL20
LED101: GN/MSX; LED3MM
LED102: GN/IOEN; LED3MM
LED103: GB/IOEN; LED3MM
R101, R102, R103: 10k; 0207/10
RN101: 4k7; SIL9
S101: PROG; TL3XPO
SLOT101: MSXSLOT-CARD; MSXCARD
SV101: ML343MLE; 3M_34L

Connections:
0X4X: IC103.16 (O2), IC109.3 (I1)
0X40_RD: IC103.15 (O1), IC105.10 (I8)
0X40_WR: IC103.14 (O0), IC105.1 (CLK/I0)
+5V: C101.2, C102.2, C103.2, C104.2, IC101.20 (VCC), IC102.28 (VCC), IC103.24 (VCC), IC104.20 (VCC), IC105.24 (VCC), IC106.20 (VCC), IC107.28 (VCC), IC108.14 (VCC), IC109.24 (VCC), IC110.20 (VCC), LED101.A, LED102.A, R101.2, R102.1, R103.1, RN101.1, SLOT101.A23 (+5VA), SLOT101.A24 (+5VB)
/BUSDIR: D102.A, SLOT101.B5 (/BUSDIR)
/CS1: IC107.22 (!OE), IC109.10 (I8), SLOT101.A1 (/CS1)
/DIR: D102.C, IC109.18 (O4)
/DISINT: IC108.5 (I1), IC109.20 (O6)
/ENAINT: IC104.19 (G), IC108.1 (I0), IC109.17 (O3)
/GETINT: IC103.23 (O9), IC109.16 (O2)
/INT: D101.A, SLOT101.B4 (/INT)
/INT0#: IC101.11 (B8), RN101.9, SV101.16
/INT1#: IC101.12 (B7), RN101.8, SV101.14
/INT2#: IC101.13 (B6), RN101.7, SV101.12
/INT3#: IC101.14 (B5), RN101.6, SV101.10
/INT4#: IC101.15 (B4), RN101.5, SV101.8
/INT5#: IC101.16 (B3), RN101.4, SV101.6
/INT6#: IC101.17 (B2), RN101.3, SV101.4
/INT7#: IC101.18 (B1), RN101.2, SV101.2
/INT#: D101.C, IC109.14 (O0)
/INTA: IC102.26 (INTA), IC103.21 (O7)
/INTZ80#: IC104.17 (B2), IC109.11 (I9), R102.2, SV101.25
/IOEN: IC103.1 (CLK/I0), IC105.15 (O1), IC109.6 (I4), LED102.K (C)
/IORQ: IC103.10 (I8), IC109.5 (I3), SLOT101.A6 (/IORQ)
/IORQ#: IC109.22 (O8), SV101.26
/M1: IC103.11 (I9), SLOT101.A5 (/M1)
/M1#: IC103.17 (O3), SV101.29
/PIC: IC102.1 (CS), IC103.20 (O6)
/RCDIR: IC106.1 (DIR), IC109.19 (O5)
/RD: IC102.3 (RD), IC103.13 (I10), IC109.8 (I6), SLOT101.B7 (/RD)
/RD#: IC103.18 (O4), SV101.27
/RESET: IC105.11 (I9), IC109.15 (O1), SLOT101.A8 (/RES), SV101.31
/SLTSL: IC107.20 (!CS), IC109.9 (I7), SLOT101.B2 (/SLTSL)
/WAIT: SLOT101.A4 (/WAIT), SV101.32
/WE: IC107.27 (!WE), R103.2, S101.3 (S)
/WEX: S101.2, SLOT101.A3 (NC0)
/WR: IC102.2 (WR), IC103.2 (I0), IC109.7 (I5), SLOT101.A7 (/WR)
/WR#: IC109.21 (O7), SV101.28
A0: IC102.27 (A0), IC103.9 (I7), IC107.10 (A0), SLOT101.B14 (A0)
A0#: IC110.12 (8Q), SV101.24
A1: IC103.8 (I6), IC107.9 (A1), SLOT101.A14 (A1)
A1#: IC110.13 (7Q), SV101.23
A2: IC103.7 (I5), IC107.8 (A2), SLOT101.B15 (A2)
A2#: IC110.14 (6Q), SV101.22
A3: IC103.6 (I4), IC107.7 (A3), SLOT101.A15 (A3)
A3#: IC110.15 (5Q), SV101.21
A4: IC103.5 (I3), IC107.6 (A4), SLOT101.B16 (A4)
A4#: IC110.16 (4Q), SV101.20
A5: IC103.4 (I2), IC107.5 (A5), SLOT101.A16 (A5)
A5#: IC110.17 (3Q), SV101.19
A6: IC107.4 (A6), IC108.10 (I1), SLOT101.B11 (A6)
A6#: IC110.18 (2Q), SV101.18
A7: IC107.3 (A7), IC108.12 (I0), IC108.13 (I1), SLOT101.A11 (A7)
A7#: IC110.19 (1Q), SV101.17
A8: IC107.25 (A8), SLOT101.B12 (A8)
A9: IC107.24 (A9), SLOT101.A9
A10: IC107.21 (A10), SLOT101.B10 (A10)
A11: IC107.23 (A11), SLOT101.A10 (A11)
A12: IC107.2 (A12), SLOT101.A12
A13: IC107.26 (A13), SLOT101.B13 (A13)
A14: IC107.1 (A14), SLOT101.A13 (A14)
A15: SLOT101.B9 (A15)
ALE: IC103.22 (O8), IC110.11 (CLK)
AX: IC103.3 (I1), IC108.8 (O)
CLK: IC109.2 (I0), SLOT101.B21 (CLK)
CLK#: IC109.23 (O9), SV101.30
D0: IC102.11 (D0), IC104.9 (A8), IC105.9 (I7), IC105.16 (O2), IC106.9 (A8), IC107.11 (I/O0), IC110.9 (8D), SLOT101.B17 (D0)
D0#: IC106.11 (B8), SV101.15
D1: IC102.10 (D1), IC104.8 (A7), IC105.8 (I6), IC105.17 (O3), IC106.8 (A7), IC107.12 (I/O1), IC110.8 (7D), SLOT101.A17 (D1)
D1#: IC106.12 (B7), SV101.13
D2: IC102.9 (D2), IC104.7 (A6), IC105.7 (I5), IC105.18 (O4), IC106.7 (A6), IC107.13 (I/O2), IC110.7 (6D), SLOT101.B18 (D2)
D2#: IC106.13 (B6), SV101.11
D3: IC102.8 (D3), IC104.6 (A5), IC105.6 (I4), IC105.19 (O5), IC106.6 (A5), IC107.15 (I/O3), IC110.6 (5D), SLOT101.A18 (D3)
D3#: IC106.14 (B5), SV101.9
D4: IC102.7 (D4), IC104.5 (A4), IC105.5 (I3), IC105.20 (O6), IC106.5 (A4), IC107.16 (I/O4), IC110.5 (4D), SLOT101.B19 (D4)
D4#: IC106.15 (B4), SV101.7
D5: IC102.6 (D5), IC104.4 (A3), IC105.4 (I2), IC105.21 (O7), IC106.4 (A3), IC107.17 (I/O5), IC110.4 (3D), SLOT101.A19 (D5)
D5#: IC106.16 (B3), SV101.5
D6: IC102.5 (D6), IC104.3 (A2), IC105.3 (I1), IC105.22 (O8), IC106.3 (A2), IC107.18 (I/O6), IC110.3 (2D), SLOT101.B20 (D6)
D6#: IC106.17 (B2), SV101.3
D7: IC102.4 (D7), IC104.2 (A1), IC105.2 (I0), IC105.23 (O9), IC106.2 (A1), IC107.19 (I/O7), IC110.2 (1D), SLOT101.A20 (D7)
D7#: IC106.18 (B1), SV101.1
GND: C101.1, C102.1, C103.1, C104.1, IC101.1 (DIR), IC101.10 (GND), IC101.19 (G), IC102.14 (GND), IC103.12 (GND), IC104.1 (DIR), IC104.10 (GND), IC104.11 (B8), IC104.12 (B7), IC104.13 (B6), IC104.14 (B5), IC104.15 (B4), IC104.16 (B3), IC105.12 (GND), IC106.10 (GND), IC106.19 (G), IC107.14 (VSS), IC108.7 (GND), IC109.12 (GND), IC110.1 (OC), IC110.10 (GND), LED101.K (C), LED103.K (C), SLOT101.A21 (GNDA), SLOT101.A22 (GNDB), SV101.33, SV101.34
INT0: IC101.9 (A8), IC102.18 (IR0)
INT1: IC101.8 (A7), IC102.19 (IR1)
INT2: IC101.7 (A6), IC102.20 (IR2)
INT3: IC101.6 (A5), IC102.21 (IR3)
INT4: IC101.5 (A4), IC102.22 (IR4)
INT5: IC101.4 (A3), IC102.23 (IR5)
INT6: IC101.3 (A2), IC102.24 (IR6)
INT7: IC101.2 (A1), IC102.25 (IR7)
INTEN: IC108.3 (O), IC108.4 (I0), IC109.1 (CLK/I0), LED103.A
INTPIC: IC102.17 (INT), IC104.18 (B1), IC109.13 (I10)
unnamed: IC102.16 (SP/EN), R101.1
unnamed: IC108.2 (I1), IC108.6 (O)
unnamed: SLOT101.B22 (SW1), SLOT101.B23 (SW2)
unnamed: IC108.9 (I0), IC108.11 (O)
RC2014: IC103.19 (O5), IC109.4 (I2)

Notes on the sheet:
MSX-IO-Expander Buffer, ADDR-Decoder & IM2-Mode-Decoder (c) Dr.-Ing. Thomas Wiesner
I/O address Device-ID: 192 / 0xC0 0x40 = Switched IO Manufactor 0x41 = GET Interruptchannel 0x42 = /CS-PIC A0=0 0x43 = /CS-PIC A0=1 0x44 = INTA-READ 0x45 = IM2-READ 0x46 = Set I/O-Address 0x47 = READ/WRITE I/O 0x48...0x4f = n.c.

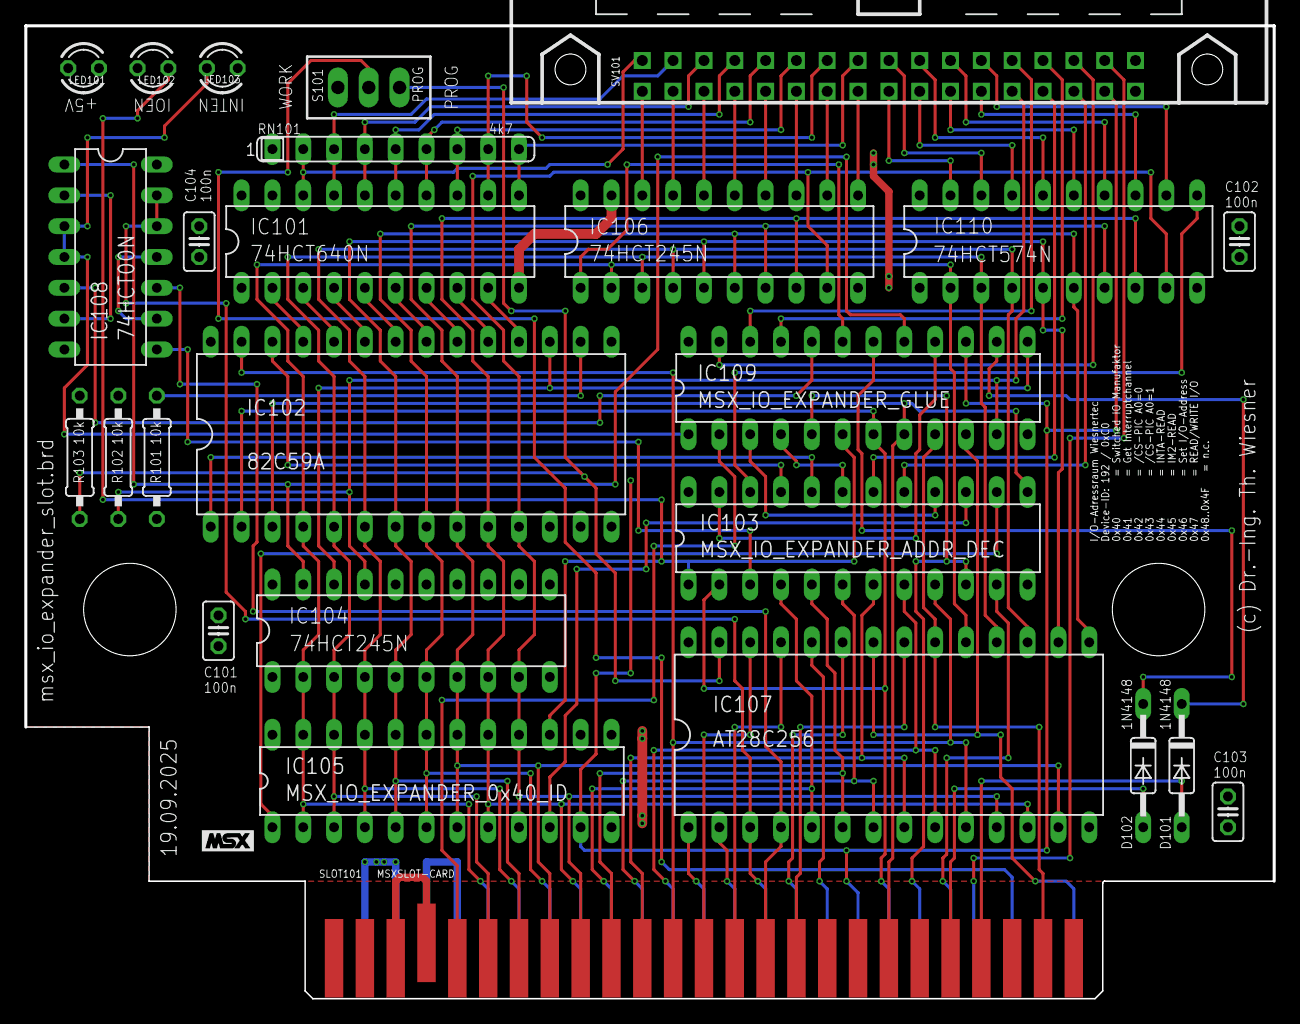
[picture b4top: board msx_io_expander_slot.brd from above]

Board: 2 copper layers, 102.9 x 80.2 mm, 26 parts (0 on the bottom side), 97 nets.
